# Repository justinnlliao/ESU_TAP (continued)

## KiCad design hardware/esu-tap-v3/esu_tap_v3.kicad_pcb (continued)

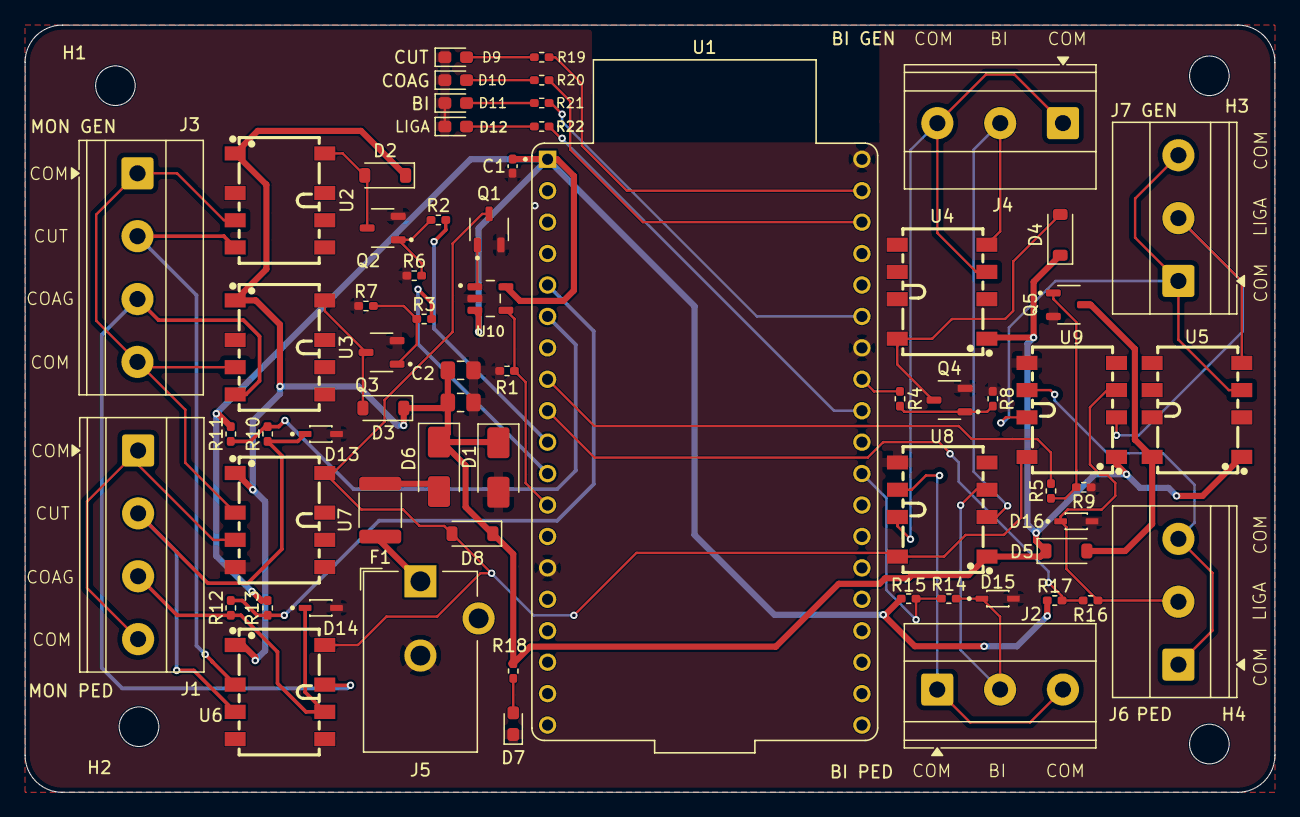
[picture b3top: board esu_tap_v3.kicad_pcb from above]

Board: 2 copper layers, 101.0 x 62.0 mm, 68 parts (0 on the bottom side), 47 nets.

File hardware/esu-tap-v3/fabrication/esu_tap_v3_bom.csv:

"Comment","Designator","Footprint","LCSC Part #"
"100n","C1","Capacitor_SMD:C_0402_1005Metric_Pad0.74x0.62mm_HandSolder","C1525"
"100n","C2","Capacitor_SMD:C_0805_2012Metric_Pad1.18x1.45mm_HandSolder","C49678"
"22u","C3","Capacitor_SMD:C_0805_2012Metric_Pad1.18x1.45mm_HandSolder","C296720"
"SMAJ6.0A","D1","Diode_SMD:D_SMA","C364284"
"1N4148W","D2,D3,D4,D5,D8","Diode_SMD:D_SOD-123","C81598"
"SS24","D6","Diode_SMD:D_SMA","C115726"
"BLUE","D7,D9","LED_SMD:LED_0603_1608Metric_Pad1.05x0.95mm_HandSolder","C2288"
"RED","D10","LED_SMD:LED_0603_1608Metric_Pad1.05x0.95mm_HandSolder","C2286"
"YELLOW","D11,D12","LED_SMD:LED_0603_1608Metric_Pad1.05x0.95mm_HandSolder","C2287"
"PESD5V0S1BA","D13,D14,D15,D16","PESD5V0S1BA_DG_115:SOD2613X115N","C19224"
"PTC 1.10A hold","F1","Fuse_1812_PTC:Fuse_1812_4532Metric","C142746"
"AO3400A","Q1,Q2,Q3,Q4,Q5","AO3400A:SOT95P280X125-3N","C20917"
"1k","R1,R2,R3,R4,R5,R10,R12,R14,R16","Resistor_SMD:R_0402_1005Metric_Pad0.72x0.64mm_HandSolder","C11702"
"10k","R6,R7,R8,R9,R11,R13,R15,R17","Resistor_SMD:R_0402_1005Metric_Pad0.72x0.64mm_HandSolder","C60490"
"680","R18,R19,R20,R21,R22","Resistor_SMD:R_0402_1005Metric_Pad0.72x0.64mm_HandSolder","C137948"
"G6K-2F-Y-5V_C2982926","U2,U3,U4,U5,U6,U7,U8,U9","G6K-2F-Y:RELAY-SMD_G6K-2F-Y","C2982926"
"TPS3823A-33DBVR","U10","TPS3823A-33DBVR:SOT95P280X145-5N","C702191"

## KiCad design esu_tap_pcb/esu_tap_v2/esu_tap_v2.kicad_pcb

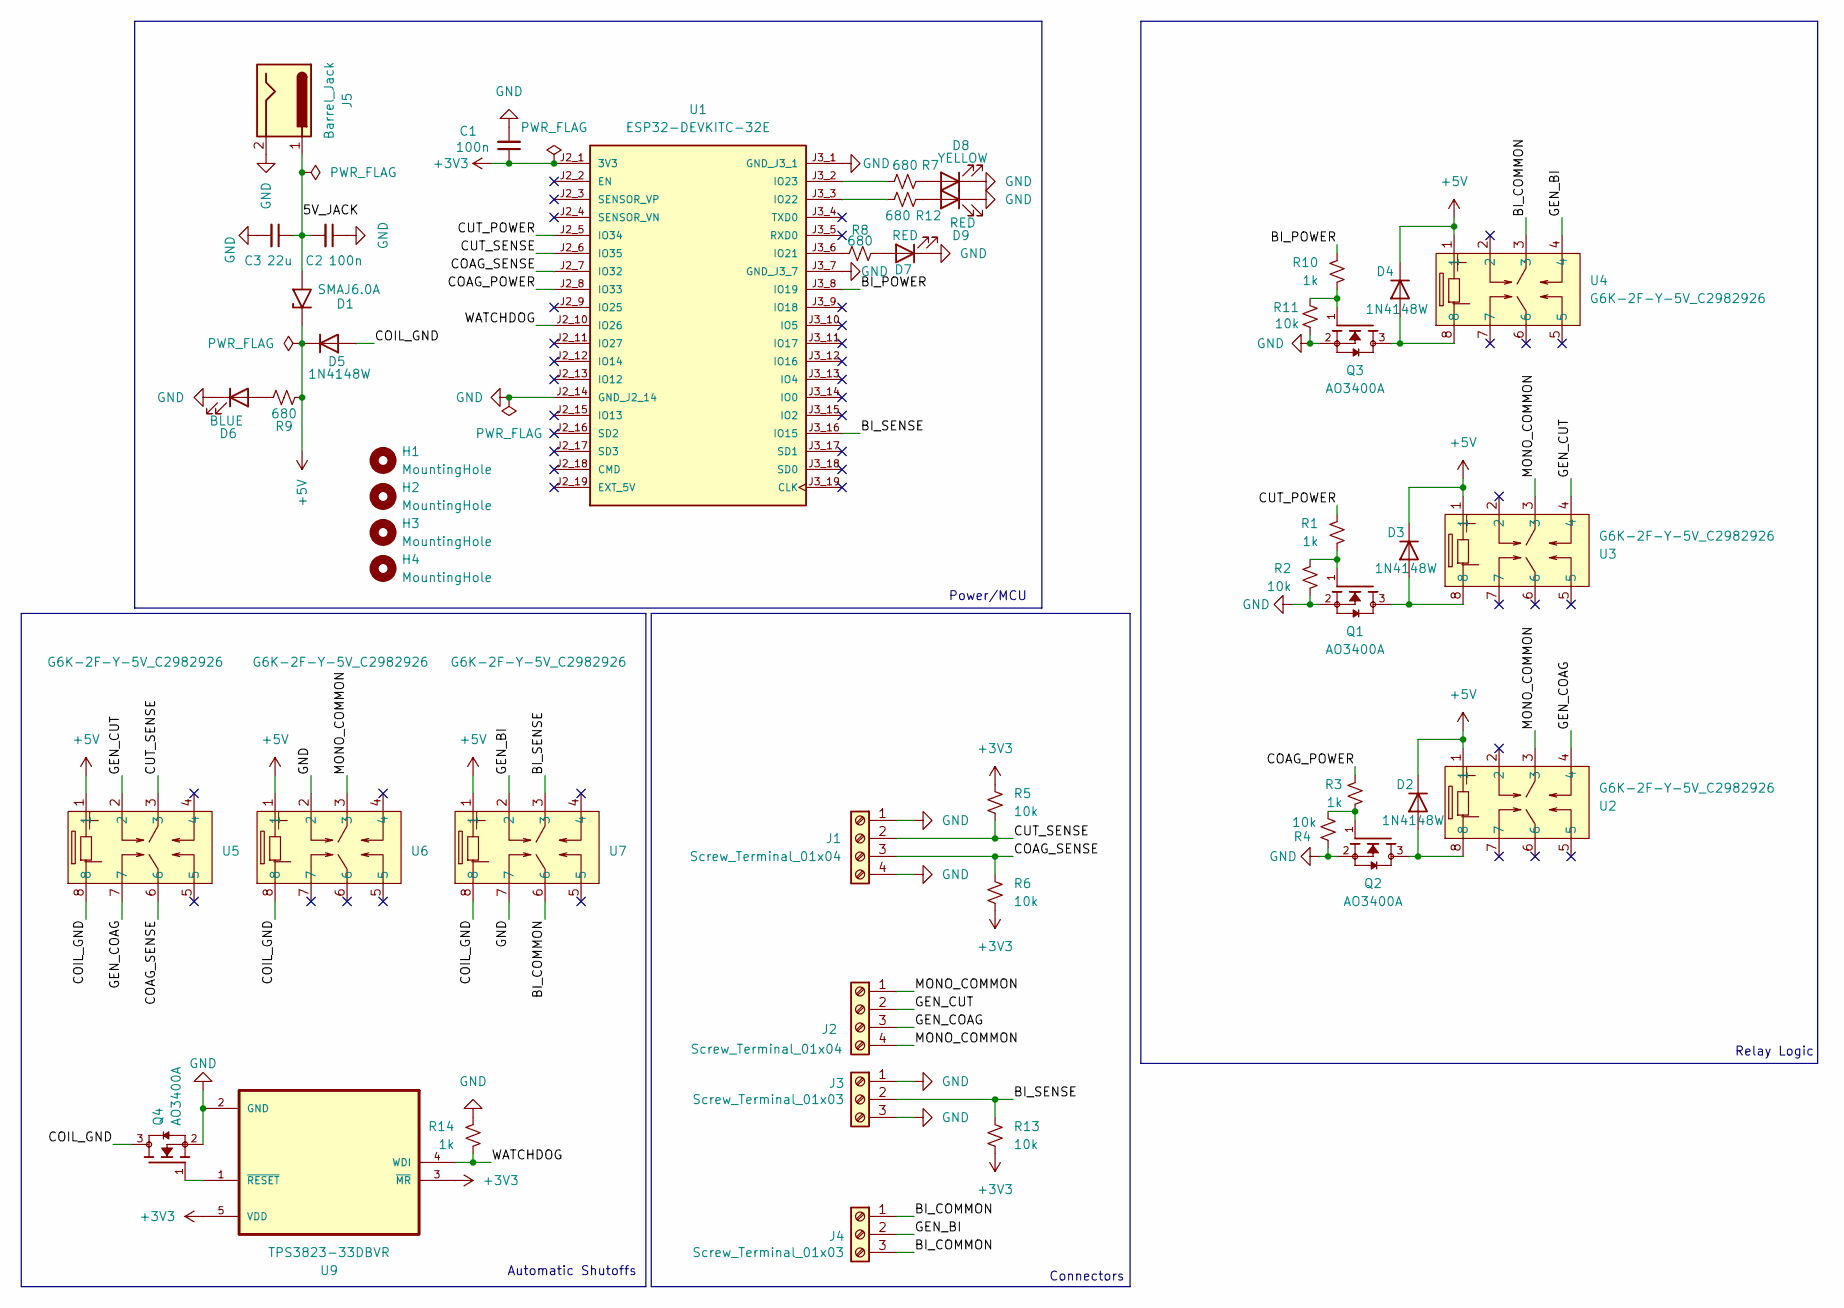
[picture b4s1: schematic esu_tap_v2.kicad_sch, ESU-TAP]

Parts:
C1, C2: 100n; C_0402_1005Metric_Pad0.74x0.62mm_HandSolder; LCSC C1525
C3: 22u; C_0402_1005Metric_Pad0.74x0.62mm_HandSolder; LCSC C22367823
D1: SMAJ6.0A; D_SMA
D2, D3, D4, D5: 1N4148W; D_SOD-123; LCSC C81598
D6: BLUE; LED_0603_1608Metric_Pad1.05x0.95mm_HandSolder; LCSC C2290
D7, D9: RED; LED_0603_1608Metric_Pad1.05x0.95mm_HandSolder; LCSC C2286
D8: YELLOW; LED_0603_1608Metric_Pad1.05x0.95mm_HandSolder; LCSC C2287
H1, H2, H3, H4: MountingHole; MountingHole_3.2mm_M3_DIN965
J1, J2: Screw_Terminal_01x04; TerminalBlock_Phoenix_MKDS-1,5-4-5.08_1x04_P5.08mm_Horizont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
J3, J4: Screw_Terminal_01x03; TerminalBlock_Phoenix_MKDS-1,5-3-5.08_1x03_P5.08mm_Horizont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
J5: Barrel_Jack; BarrelJack_CUI_PJ-102AH_Horizontal
Q1, Q2, Q3, Q4: AO3400A; SOT95P280X125-3N; PARTREV L
R1, R3, R10, R14: 1k; R_0402_1005Metric_Pad0.72x0.64mm_HandSolder; LCSC C11702
R2, R4, R5, R6, R11, R13: 10k; R_0402_1005Metric_Pad0.72x0.64mm_HandSolder; LCSC C2889342
R7, R8, R9, R12: 680; R_0402_1005Metric_Pad0.72x0.64mm_HandSolder; LCSC C25130
U1: ESP32-DEVKITC-32E; MODULE_ESP32-DEVKITC-32E; PARTREV 1.4
U2, U3, U4, U5, U6, U7: G6K-2F-Y-5V_C2982926; RELAY-SMD_G6K-2F-Y; MPN G6K-2F-Y-5V; LCSC C2982926
U9: TPS3823-33DBVR; SOT95P280X145-5N

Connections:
+3V3: C1.1, R5.1, R6.2, R13.2, U1.J2_1 (3V3), U9.3 (~MR), U9.5 (VDD)
+5V: D1.1 (A1), D2.1 (K), D3.1 (K), D4.1 (K), D5.1 (K), R9.1, U2.1, U3.1, U4.1, U5.1, U6.1, U7.1
/5V_JACK: C2.2, C3.1, D1.2 (A2), J5.1
/BI_COMMON: J4.1, J4.3, U4.3, U7.6
/BI_POWER: R10.2, U1.J3_8 (IO19)
/BI_SENSE: J3.2, R13.1, U1.J3_16 (IO15), U7.3
/COAG_POWER: R3.2, U1.J2_8 (IO33)
/COAG_SENSE: J1.3, R6.1, U1.J2_7 (IO32), U5.6
/COIL_GND: D5.2 (A), Q4.3, U5.8, U6.8, U7.8
/CUT_POWER: R1.2, U1.J2_5 (IO34)
/CUT_SENSE: J1.2, R5.2, U1.J2_6 (IO35), U5.3
/GEN_BI: J4.2, U4.4, U7.2
/GEN_COAG: J2.3, U2.4, U5.7
/GEN_CUT: J2.2, U3.4, U5.2
/MONO_COMMON: J2.1, J2.4, U2.3, U3.3, U6.3
/WATCHDOG: R14.1, U1.J2_10 (IO26), U9.4 (WDI)
GND: C1.2, C2.1, C3.2, D6.1 (K), D7.1 (K), D8.1 (K), D9.1 (K), J1.1, J1.4, J3.1, J3.3, J5.2, Q1.2, Q2.2, Q3.2, Q4.2, R2.2, R4.2, R11.1, R14.2, U1.J2_14 (GND_J2_14), U1.J3_1 (GND_J3_1), U1.J3_7 (GND_J3_7), U6.2, U7.7, U9.2 (GND)
unnamed: D2.2 (A), Q2.3, U2.8
unnamed: D3.2 (A), Q1.3, U3.8
unnamed: D4.2 (A), Q3.3, U4.8
unnamed: D6.2 (A), R9.2
unnamed: D7.2 (A), R8.2
unnamed: D8.2 (A), R7.2
unnamed: D9.2 (A), R12.2
unnamed: Q1.1, R1.1, R2.1
unnamed: Q2.1, R3.1, R4.1
unnamed: Q3.1, R10.1, R11.2
unnamed: R8.1, U1.J3_6 (IO21)
unnamed: R12.1, U1.J3_3 (IO22)
unnamed: R7.1, U1.J3_2 (IO23)
unnamed: Q4.1, U9.1 (~RESET)

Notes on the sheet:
Automatic Shutoffs
Connectors
Relay Logic
Power/MCU

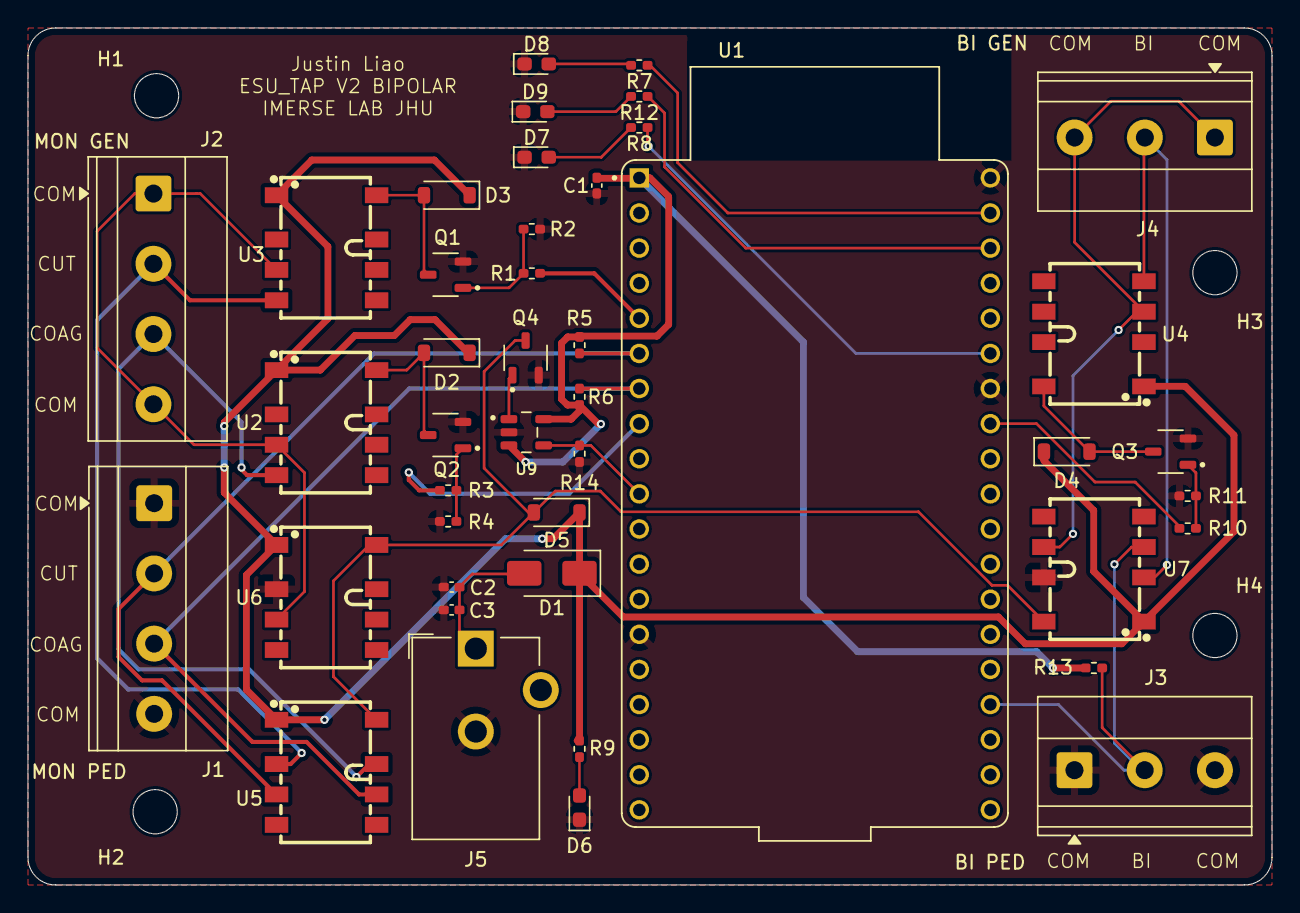
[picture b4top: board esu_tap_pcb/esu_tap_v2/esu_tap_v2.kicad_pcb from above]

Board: 2 copper layers, 90.0 x 62.0 mm, 47 parts (0 on the bottom side), 31 nets.

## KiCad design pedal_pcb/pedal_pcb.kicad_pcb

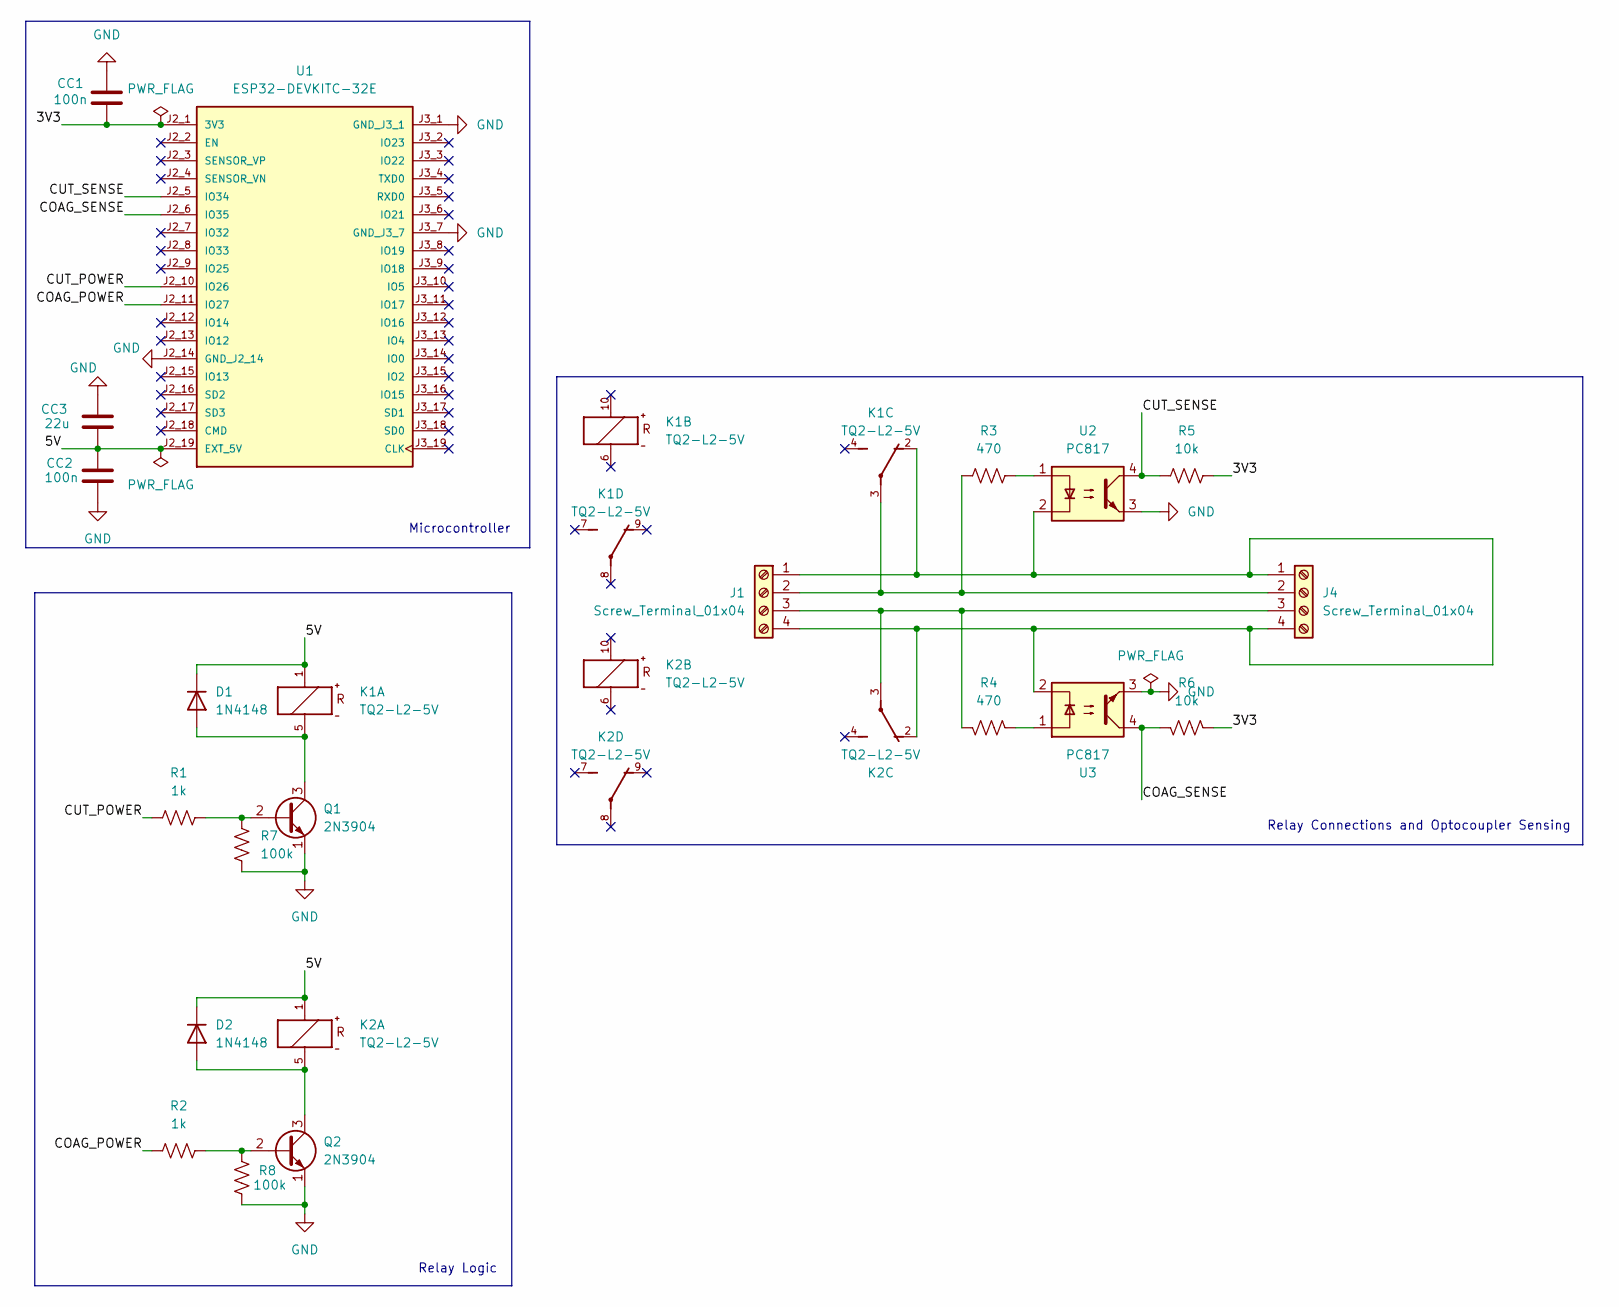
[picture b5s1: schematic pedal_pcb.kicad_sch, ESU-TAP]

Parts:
CC1, CC2: 100n; C_0603_1608Metric_Pad1.08x0.95mm_HandSolder
CC3: 22u; C_0603_1608Metric_Pad1.08x0.95mm_HandSolder
D1, D2: 1N4148; D_DO-35_SOD27_P7.62mm_Horizontal
J1, J4: Screw_Terminal_01x04; TerminalBlock_Phoenix_MKDS-1,5-4-5.08_1x04_P5.08mm_Horizont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
K1, K2: TQ2-L2-5V; TQ2; FARNELL 1175718
Q1, Q2: 2N3904; TO-92_Inline
R1, R2: 1k; R_0603_1608Metric_Pad0.98x0.95mm_HandSolder
R3, R4: 470; R_0603_1608Metric_Pad0.98x0.95mm_HandSolder
R5, R6: 10k; R_0603_1608Metric_Pad0.98x0.95mm_HandSolder
R7, R8: 100k; R_0603_1608Metric_Pad0.98x0.95mm_HandSolder
U1: ESP32-DEVKITC-32E; MODULE_ESP32-DEVKITC-32E; PARTREV 1.4
U2, U3: PC817; DIP-4_W7.62mm

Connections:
/3V3: CC1.1, R5.2, R6.2, U1.J2_1 (3V3)
/5V: CC2.2, CC3.1, D1.1 (K), D2.1 (K), K1.1, K2.1, U1.J2_19 (EXT_5V)
/COAG_POWER: R2.1, U1.J2_11 (IO27)
/COAG_SENSE: R6.1, U1.J2_6 (IO35), U3.4
/CUT_POWER: R1.1, U1.J2_10 (IO26)
/CUT_SENSE: R5.1, U1.J2_5 (IO34), U2.4
GND: CC1.2, CC2.1, CC3.2, Q1.1 (E), Q2.1 (E), R7.1, R8.1, U1.J2_14 (GND_J2_14), U1.J3_1 (GND_J3_1), U1.J3_7 (GND_J3_7), U2.3, U3.3
unnamed: D1.2 (A), K1.5, Q1.3 (C)
unnamed: D2.2 (A), K2.5, Q2.3 (C)
unnamed: J1.1, J1.4, J4.1, J4.4, K1.2, K2.2, U2.2, U3.2
unnamed: J1.2, J4.2, K1.3, R3.1
unnamed: J1.3, J4.3, K2.3, R4.1
unnamed: Q1.2 (B), R1.2, R7.2
unnamed: Q2.2 (B), R2.2, R8.2
unnamed: R3.2, U2.1
unnamed: R4.2, U3.1

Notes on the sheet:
Relay Connections and Optocoupler Sensing
Relay Logic
Microcontroller

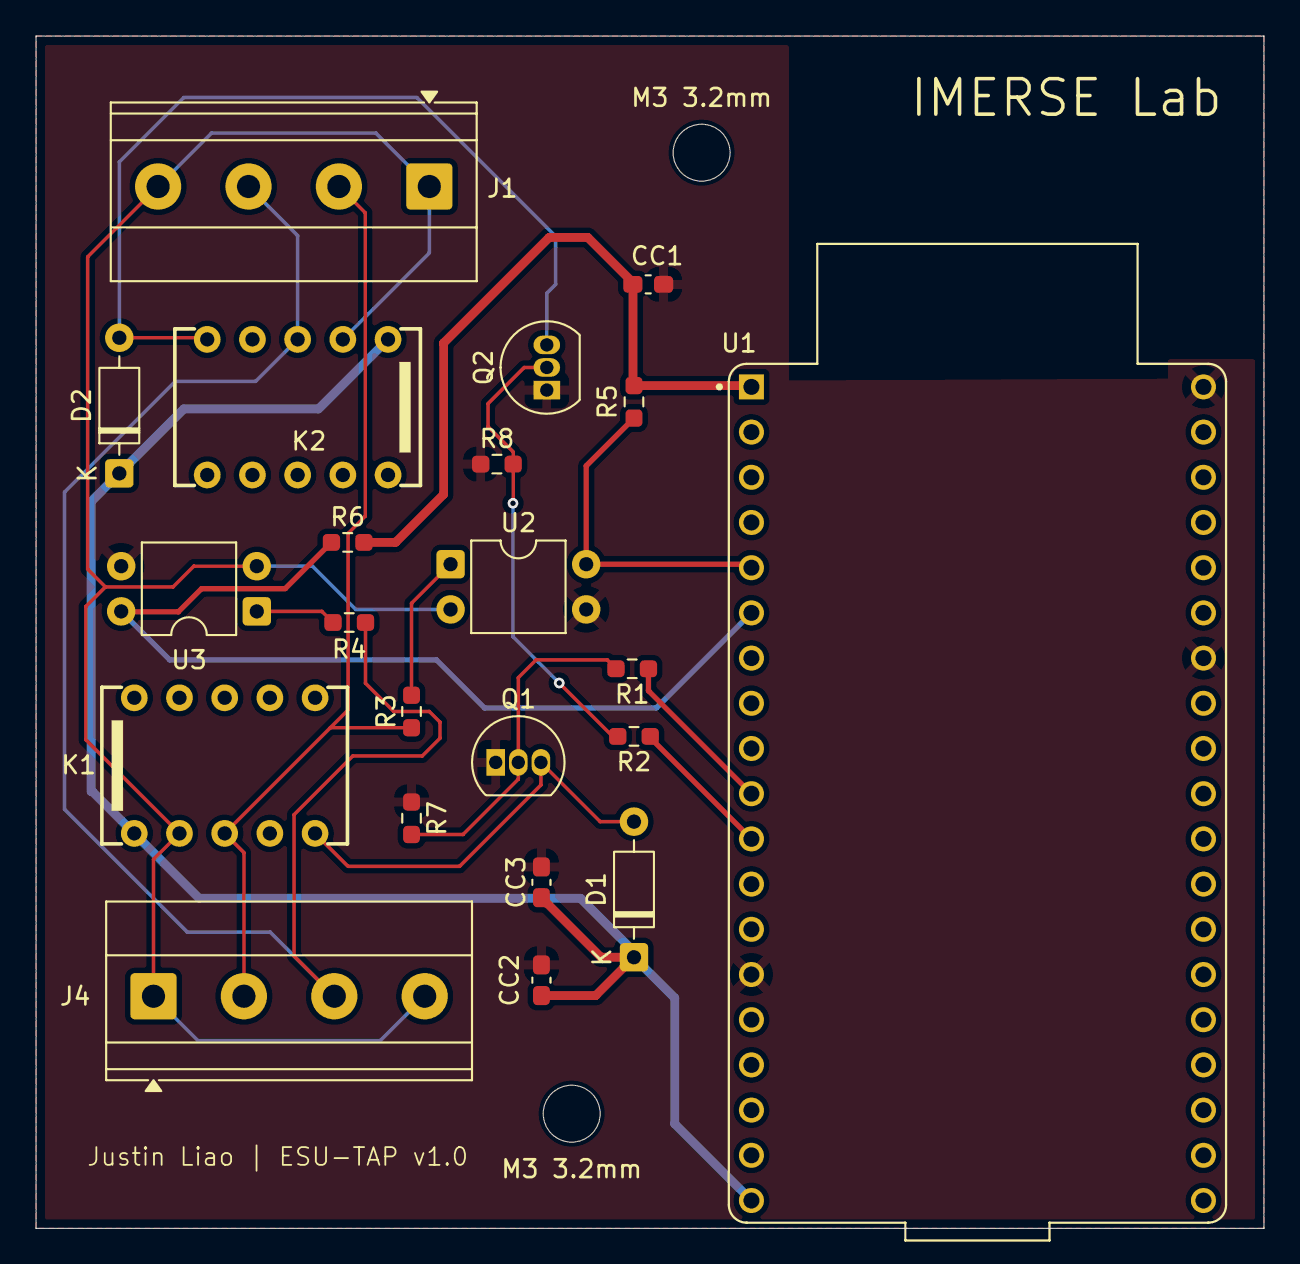
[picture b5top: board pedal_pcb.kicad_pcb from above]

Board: 2 copper layers, 69.0 x 67.0 mm, 24 parts (0 on the bottom side), 16 nets.

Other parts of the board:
M3 3.2mm, M3 3.2mm#2: MountingHole_3.2mm_M3

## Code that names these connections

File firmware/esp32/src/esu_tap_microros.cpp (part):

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// ----------------------------- Pin map (v2) ------------------------
// Sense inputs: PEDAL dry contacts, read directly. LOW = pedal pressed.
// These do NOT reflect relay state.
const int PIN_SENSE_CUT  = 35;   // CUT_SENSE  (IO35) -- swapped vs v1 to match board
const int PIN_SENSE_COAG = 34;   // COAG_SENSE (IO34)
const int PIN_SENSE_BI   = 17;   // BI_SENSE   (IO17)

// Relay drives (HIGH = relay closed = generator activated)
const int PIN_RELAY_CUT  = 26;   // CUT_CTRL
const int PIN_RELAY_COAG = 27;   // COAG_CTRL
const int PIN_RELAY_BI   = 19;   // BI_CTRL

// Status LEDs (active-HIGH)
const int PIN_LED_CUT    = 23;   // D8
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int lastRawCut = 0, lastRawCoag = 0, lastRawBi = 0;
unsigned long lastRawChangeCutMs = 0, lastRawChangeCoagMs = 0, lastRawChangeBiMs = 0;

// Watchdog pet: toggle PIN_WDT on an interval well inside the ~1.6 s timeout.
// The timeout has wide production tolerance (~0.9-2.5 s), so pet FAST.
const unsigned long WDT_TOGGLE_MS = 250;
unsigned long lastWdtToggleMs = 0;
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
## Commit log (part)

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2026-04-24 ros2 package
2026-06-04 progress on pcb schematic and updated readmes
2026-06-04 made pcb design
2026-06-04 added silkscreen to pcb
2026-06-08 schematic and pcb update
    removed ground under antenna removed en pullup
2026-06-08 added another coupling capacitor to 5V rail
2026-06-08 removed bunch of random images that appeared
2026-06-08 i honestly dont know what happened git issues
